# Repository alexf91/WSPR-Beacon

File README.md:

# WSPR Beacon

## IMPORTANT ##

The firmware in this repository was not tested with the PCB design in the
respository.
It was tested on a prototype board with a 3.3V version of an Arduino Nano and a
Si5351 breakout board.

## Getting started

The firmware is built using CMake and requires an installation of `avr-gcc`.

```
cd firmware
mkdir build
cd build
cmake -DCMAKE_BUILD_TYPE=Release ..
make
make flash
```

The beacon is controlled with the `wsprctrl` tool in the `software` directory.
It is written in Python 3 and requires `pyusb`. It is used to set the location,
callsign, frequency and power of the beacon and starts the transmission.
The beacon keeps these settings in memory, so they only have to be set after
a reset. Saving settings to EEPROM is planned.

```
./wsprctrl --correction 26.5
./wsprctrl --drive 8
./wsprctrl --lat 48.210033 --lon 16.363449
./wsprctrl --frequency 7040150
./wsprctrl --call OE5TKM
./wsprctrl --wspr
```

It's also possible to combine multiple options.

## Prototype

* Atmega328 with V-USB for control
* Si5351 with 3 clock outputs (one output per band)
* 40/30/20 meters
* Powered and controlled via USB

### Filter Design

Filter values are taken from [here](https://dk4sx.darc.de/txtp.htm).

## Libraries

* V-USB: http://vusb.wikidot.com/
* Si5351: https://github.com/etherkit/si5351-avr-tiny-minimal/
* I2C: https://github.com/g4lvanix/I2C-master-lib
* UART: http://homepage.hispeed.ch/peterfleury/index.html

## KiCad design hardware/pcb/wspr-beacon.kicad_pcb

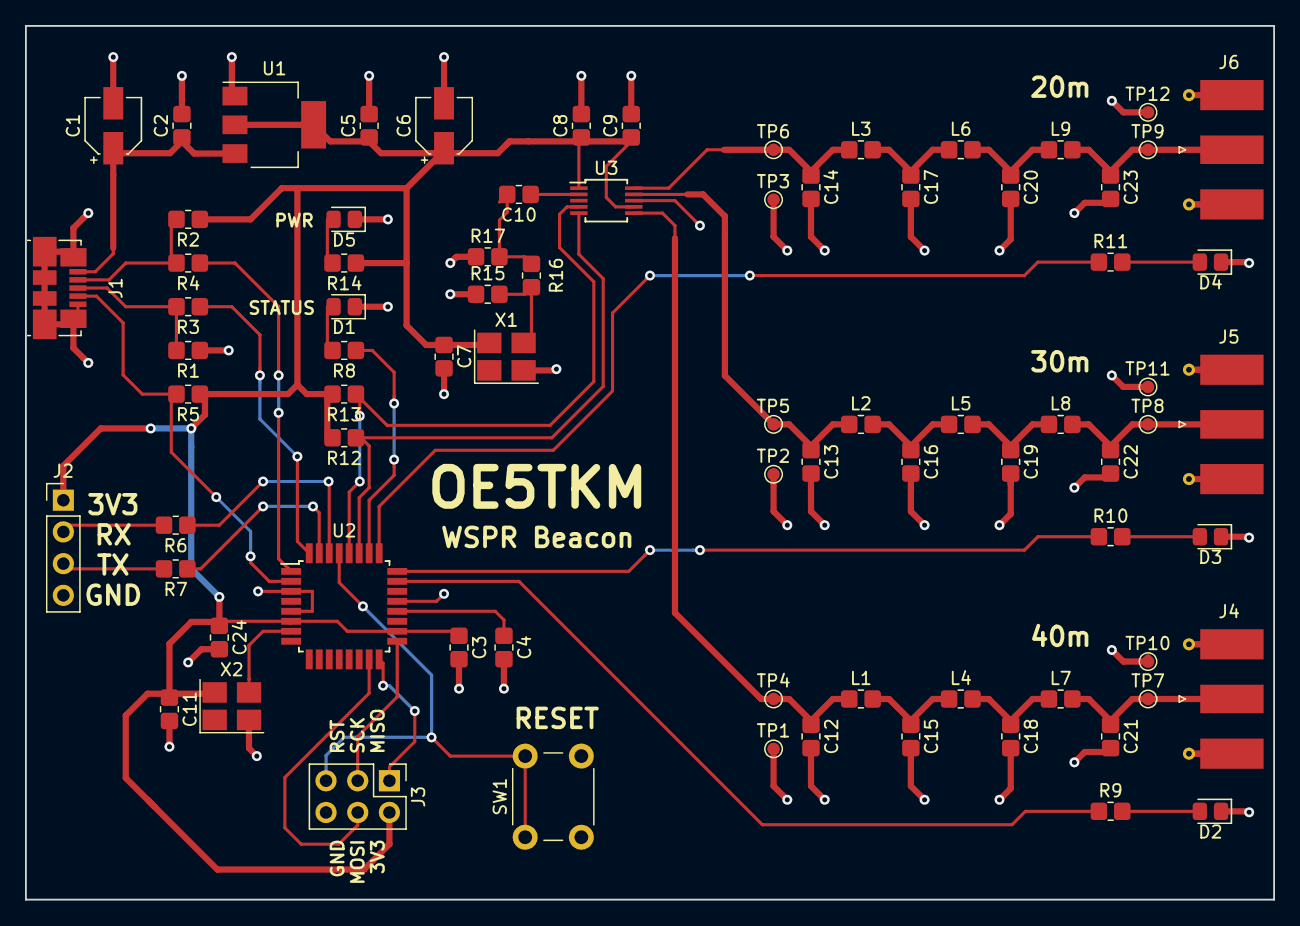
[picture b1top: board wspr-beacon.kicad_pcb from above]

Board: 2 copper layers, 100.0 x 70.0 mm, 79 parts (0 on the bottom side), 44 nets.

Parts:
C1, C6: 4u7; CP_Elec_4x4.5
C2, C3, C4, C5, C7, C8, C9, C10, C11, C24: 100n; C_0805_2012Metric_Pad1.33x1.40mm_HandSolder
C12, C21: 430p; C_0805_2012Metric_Pad1.33x1.40mm_HandSolder
C13, C22: 300p; C_0805_2012Metric_Pad1.33x1.40mm_HandSolder
C14, C23: 220p; C_0805_2012Metric_Pad1.33x1.40mm_HandSolder
C15, C18: 820p; C_0805_2012Metric_Pad1.33x1.40mm_HandSolder
C16, C19: 560p; C_0805_2012Metric_Pad1.33x1.40mm_HandSolder
C17, C20: 390p; C_0805_2012Metric_Pad1.33x1.40mm_HandSolder
D1, D2, D3, D4, D5: LED; LED_0805_2012Metric_Pad1.15x1.40mm_HandSolder
J1: USB_OTG; USB_Micro-B_Molex_47346-0001
J2: Conn_01x04; PinHeader_1x04_P2.54mm_Vertical
J3: Conn_02x03_Odd_Even; PinHeader_2x03_P2.54mm_Vertical
J4, J5, J6: Conn_Coaxial; SMA_Molex_73251-1153_EdgeMount_Horizontal
L1, L7: 1u5; L_0805_2012Metric_Pad1.33x1.40mm_HandSolder
L2, L8: 1u; L_0805_2012Metric_Pad1.33x1.40mm_HandSolder
L3, L9: 0.75u; L_0805_2012Metric_Pad1.33x1.40mm_HandSolder
L4: 1u8; L_0805_2012Metric_Pad1.33x1.40mm_HandSolder
L5: 1u2; L_0805_2012Metric_Pad1.33x1.40mm_HandSolder
L6: 0.91u; L_0805_2012Metric_Pad1.33x1.40mm_HandSolder
R1: 1M; R_0805_2012Metric_Pad1.33x1.40mm_HandSolder
R2: 1k5; R_0805_2012Metric_Pad1.33x1.40mm_HandSolder
R3, R4: 68; R_0805_2012Metric_Pad1.33x1.40mm_HandSolder
R5: 100k; R_0805_2012Metric_Pad1.33x1.40mm_HandSolder
R6, R7: 1k; R_0805_2012Metric_Pad1.33x1.40mm_HandSolder
R8, R9, R10, R11, R14, R15, R16, R17: R; R_0805_2012Metric_Pad1.33x1.40mm_HandSolder
R12, R13: 4k7; R_0805_2012Metric_Pad1.33x1.40mm_HandSolder
SW1: SW_Push; SW_PUSH_6mm
TP1, TP2, TP3, TP4, TP5, TP6, TP7, TP8, TP9, TP10, TP11, TP12: TEST; TestPoint_Pad_D1.0mm
U1: AP1117-33; SOT-223-3_TabPin2
U2: ATMEGA328-AU; TQFP-32_7x7mm_P0.8mm
U3: Si5351A; MSOP-10_3x3mm_P0.5mm
X1: ASE-25MHz; Oscillator_SMD_Abracon_ASE-4Pin_3.2x2.5mm_HandSoldering
X2: ASE-16MHz; Oscillator_SMD_Abracon_ASE-4Pin_3.2x2.5mm_HandSoldering

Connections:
+3V3: C3.1, C5.1, C6.1, C7.1, C8.1, C9.1, C11.1, C24.1, J2.1, J3.2, R2.1, R5.1, R12.2, R13.2, R14.1, U1.2, U2.4, U2.6, U2.18, U3.1, U3.7, X1.4, X2.4
/D+: R3.1, U2.32
/D-: R4.1, U2.1
/ID: J1.4, R5.2, U2.2
/LED_20M: R9.1, U2.23
/LED_30M: R10.1, U2.24
/LED_40M: R11.1, U2.25
/LED_ACTIVE: R8.1, U2.26
/MISO: J3.1, U2.16
/MOSI: J3.4, U2.15
/RESET: J3.5, SW1.1, U2.29
/SCK: J3.3, U2.17
/SCL: R13.1, U2.28, U3.4
/SDA: R12.1, U2.27, U3.5
GND: C1.2, C2.2, C3.2, C4.2, C5.2, C6.2, C7.2, C8.2, C9.2, C11.2, C12.2, C13.2, C14.2, C15.2, C16.2, C17.2, C18.2, C19.2, C20.2, C21.2, C22.2, C23.2, C24.2, D1.1, D2.1, D3.1, D4.1, D5.1, J1.5, J1.6, J2.4, J3.6, J4.2, J5.2, J6.2, R1.1, R15.1, R17.1, SW1.2, TP1.1, TP2.1, TP3.1, TP10.1, TP11.1, TP12.1, U1.1, U2.3, U2.5, U2.21, U3.8, X1.2, X2.2
unnamed: C4.1, U2.20
unnamed: C10.1, U3.2
unnamed: C10.2, R16.2, R17.2
unnamed: C12.1, L1.1, TP4.1, U3.6
unnamed: C13.1, L2.1, TP5.1, U3.9
unnamed: C14.1, L3.1, TP6.1, U3.10
unnamed: C15.1, L1.2, L4.1
unnamed: C16.1, L2.2, L5.1
unnamed: C17.1, L3.2, L6.1
unnamed: C18.1, L4.2, L7.1
unnamed: C19.1, L5.2, L8.1
unnamed: C20.1, L6.2, L9.1
unnamed: C21.1, J4.1, L7.2, TP7.1
unnamed: C22.1, J5.1, L8.2, TP8.1
unnamed: C23.1, J6.1, L9.2, TP9.1
unnamed: D1.2, R8.2
unnamed: D2.2, R9.2
unnamed: D3.2, R10.2
unnamed: D4.2, R11.2
unnamed: D5.2, R14.2
unnamed: J1.2, R2.2, R4.2
unnamed: J1.3, R1.2, R3.2
unnamed: J2.2, R6.2
unnamed: J2.3, R7.2
unnamed: R6.1, U2.30
unnamed: R7.1, U2.31
unnamed: R15.2, R16.1, X1.3
unnamed: U2.7, X2.3
VBUS: C1.1, C2.1, J1.1, U1.3

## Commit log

2018-06-24 Schematic for transmitter mostly finished
2018-06-24 Add schematic for USB interface
2018-06-24 Move PCB into separate directory
2018-06-24 Finish schematic and add filter simulation
2018-06-24 Add testpoints for GND
2018-06-24 Start with layout
2018-06-26 Continue with layout and add pull-ups for I2C
2018-06-26 Add reset button
2018-06-26 First finished version of layout
2018-06-26 Increase via size
2018-06-27 Update to KiCad 5
2018-06-28 Place 20m output closer to Si5351
2018-06-28 Minor layout and footprint changes
2018-06-28 Add attenuator to clock input of Si5351
2018-06-29 Increase trace width for power and RF lines
2018-07-17 Add basic working VUSB firmware
2018-07-18 Control LED over USB
2018-08-20 Add blink command to wsprctrl
2018-08-21 Add Si5253 and I2C drivers
2018-08-21 Add JT65 transmitter for testing
2018-08-21 Add WSPR encoder
2018-08-21 Set drive strength to 8mA
2018-08-21 Set drive strength from python
2018-08-21 Add testmode and other stuff
2018-08-22 Fix error when transmission should start at hh:00
2018-08-25 Use CMake as build system
2018-08-26 Start introducing more request types
2018-08-27 Encode message on beacon
2018-08-28 Cleanup
2018-08-28 Convert coordinates to grid square
2018-08-28 Update control software to new commands
2018-10-19 Add GPLv3 to base directory
    My source files already contain the license notice
2020-05-21 Enforce C99 standard to allow for initial declaration of variables in for-loop statement
2020-05-26 Optimize convolutional encoder by using Galois-type shift-registers instead of Fibonacci-type
